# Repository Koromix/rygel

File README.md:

# Projects

As a general rule, applications are licensed under the [GPL 3.0 license](https://www.gnu.org/licenses/gpl-3.0.html), whereas library code is licensed under the [MIT license](https://opensource.org/license/mit).

| Project    | Description                                                                      | Build tool | Quality  | License   |
| ---------- | -------------------------------------------------------------------------------- | ---------- | -------- | --------- |
| *blikk*    | Embeddable beginner-friendly language with static types, fast compilation        | Felix      | **WIP**  | GPL 3     |
| *core*     | Base C++ libraries (such as libcc) and small wrappers (R, rapidjson...)          | Felix      | **Good** | MIT       |
| *cnoke*    | Simple alternative to cmake.js, without any dependency                           | Node.js    | **Good** | MIT       |
| *drd*      | Alternative PMSI MCO classifier, subprojects: libdrd, drdc and drdR              | Felix/R    | **Good** | GPL 3     |
| *felix*    | Small build system made specifically for this repository                         | Felix      | **Good** | GPL 3     |
| *goupile*  | Programmable electronic data capture application                                 | Felix      | **WIP**  | GPL 3     |
| *heimdall* | Interactive timeline visualization UI                                            | Felix/R    | **WIP**  | GPL 3     |
| *hodler*   | Simple markdown-to-HTML website generator (e.g. koromix.dev)                     | Felix      | **Good** | GPL 3     |
| *koffi*    | Fast and simple C FFI (foreign function interface) for Node.js                   | Node.js    | **Good** | MIT       |
| *meestic*  | Control the keyboard lighting on MSI Delta 15 laptops                            | Felix      | **Good** | GPL 3     |
| *napka*    | List and map of mental healthcare resources in France                            | Node.js    | **WIP**  | GPL 3     |
| *redropp*  | File transfer web app with user accounts, SSO and end-to-end encryption          | Felix      | **WIP**  | GPL 3     |
| *rekkord*  | Backup tool with deduplication and asymmetric encryption                         | Felix      | **WIP**  | GPL 3     |
| *thop*     | Web-based institutional PMSI (MCO) reporting tool based on libdrd                | Felix      | **Good** | GPL 3     |
| *tytools*  | Independent tools to manage, flash and communicate with Teensy microcontrollers  | Felix      | **Good** | Unlicense |
| *web*      | Reusable utility functions and HTML/CSS/JS widgets                               | Felix      | **Good** | MIT       |

You can also visit the [attic](src/attic/) for a few more small tools.

# How to build

## C++ projects

Most projects use a dedicated build tool called felix. To get started, you need to build this tool. You can use the bootstrap scripts at the root of the repository to bootstrap it:

* Run `./bootstrap.sh` on Linux and macOS
* Run `bootstrap.bat` on Windows

This will create a felix binary at the root of the source tree. You can then start it to build all projects defined in *FelixBuild.ini*: `felix` on Windows or `./felix` on Linux and macOS.

The following compilers are supported: GCC, Clang and MSVC (on Windows). If you want to build Fast or LTO builds you also need to install Node.js in order to transpile the JS code used in some projects.

Use `./felix --help` for more information.

As of now, R packages cannot be built using this method.

## Node.js projects

Refer to each project (Koffi, etc.) documentation for instructions on how to build these projects.

## R packages

Some packages provide an Rproject file and can be built by R CMD INSTALL. Open the project file (e.g. *src/drd/drdR/drdR.Rproj*) in RStudio and use *Install and restart* in the Build tab.

Provided the needed dependencies are available (including Rtools and Rcpp), it should just work!

# Code style

## Mono repository

I've started using a single repository for all my projects in 2018 because it is easier to manage. There are two killers features for me:

* Cross-project refactoring
* Simplified dependency management

You can find a more detailed rationale here: https://danluu.com/monorepo/

## C++ flavor

Most projects are programmed in C++. I don't use the standard library much (with a few exceptions) and instead rely on my own homegrown cross-platform code, containers and abstractions.

My personal preference goes to a rather C-like C++ style:

- Careful use of templates (mainly for containers)
- Little object-oriented programming, tagged unions and code locality are preferred over inheritance and virtual methods
- Use of defer-like statements for cleanup, or RAII where it feels natural
- No exceptions, errors are logged to stderr (and/or a GUI when one exists) and propagated in the code with a simple return value (bool when possible, a dedicated enum when more information is relevant)
- Memory regions are used when many allocations are needed, when building many strings for example
- Heavy use of array and string views for function arguments
- Avoid dependencies unless a strong argument can be made for one, and vendorize them aggressively (with patches if needed)

I keep watch of all dependencies using GitHub notifications, RSS feeds, mailing lists and visual web page change detection (depending on the project), in order to update them as needed.

> [!NOTE]
> This does not apply to TyTools (and libhs), which are older than the other projects, and were made before I settled on my current programming style.

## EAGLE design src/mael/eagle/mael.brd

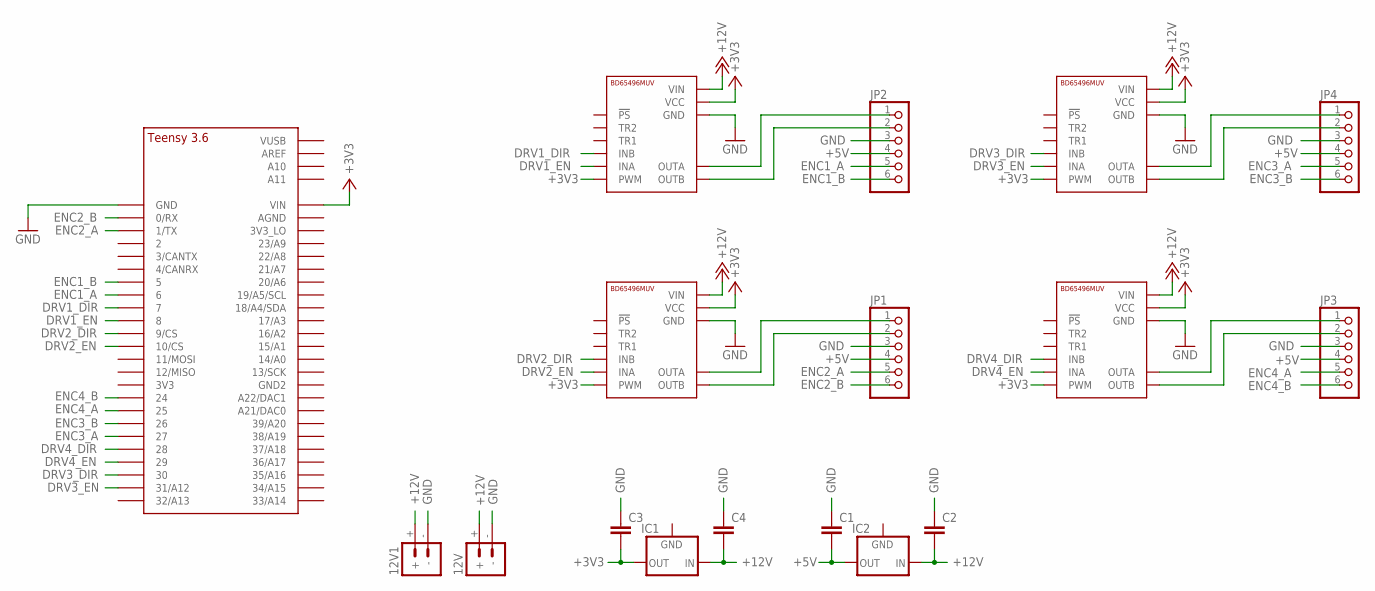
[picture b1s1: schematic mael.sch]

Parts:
12V, 12V1: BATTERY_CONN_DEANS; DEANS
C1, C2, C3, C4: C-EU050-024X044; C050-024X044
IC1, IC2: 78XXL
JP1, JP2, JP3, JP4: PINHD-1X6; 1X06
U$1, U$3, U$4, U$5: BD65496MUV
U$2: TEENSY_3.5/3.6_BASIC

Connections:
+3V3: C3.2, IC1.OUT, U$1.PWM, U$1.VCC, U$2.VIN, U$3.PWM, U$3.VCC, U$4.PWM, U$4.VCC, U$5.PWM, U$5.VCC
+5V: C1.2, IC2.OUT, JP1.4, JP2.4, JP3.4, JP4.4
+12V: 12V.+, 12V1.+, C2.2, C4.2, IC1.IN, IC2.IN, U$1.VIN, U$3.VIN, U$4.VIN, U$5.VIN
DRV1_DIR: U$1.INB, U$2.7
DRV1_EN: U$1.INA, U$2.8
DRV2_DIR: U$2.9/CS, U$3.INB
DRV2_EN: U$2.10/CS, U$3.INA
DRV3_DIR: U$2.30, U$4.INB
DRV3_EN: U$2.31/A12, U$4.INA
DRV4_DIR: U$2.28, U$5.INB
DRV4_EN: U$2.29, U$5.INA
ENC1_A: JP2.5, U$2.6
ENC1_B: JP2.6, U$2.5
ENC2_A: JP1.5, U$2.1/TX
ENC2_B: JP1.6, U$2.0/RX
ENC3_A: JP4.5, U$2.27
ENC3_B: JP4.6, U$2.26
ENC4_A: JP3.5, U$2.25
ENC4_B: JP3.6, U$2.24
GND: 12V.-, 12V1.-, C1.1, C2.1, C3.1, C4.1, JP1.3, JP2.3, JP3.3, JP4.3, U$1.GND1 (GND), U$1.GND2 (GND), U$2.GND, U$3.GND1 (GND), U$3.GND2 (GND), U$4.GND1 (GND), U$4.GND2 (GND), U$5.GND1 (GND), U$5.GND2 (GND)
unnamed: JP4.1, U$4.OUTA
unnamed: JP4.2, U$4.OUTB
unnamed: JP3.2, U$5.OUTB
unnamed: JP3.1, U$5.OUTA
unnamed: JP1.1, U$3.OUTA
unnamed: JP1.2, U$3.OUTB
unnamed: JP2.1, U$1.OUTA
unnamed: JP2.2, U$1.OUTB

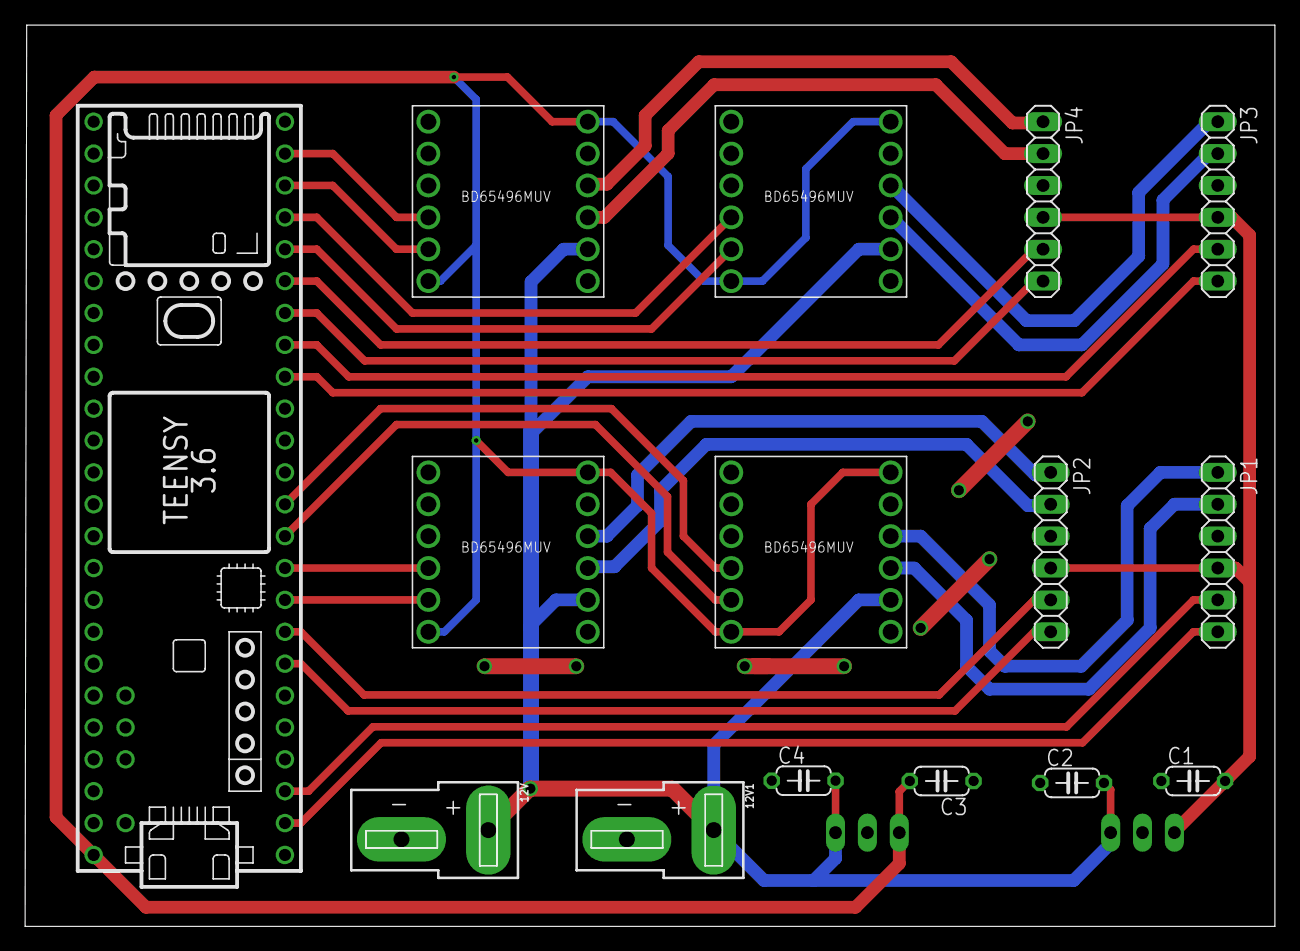
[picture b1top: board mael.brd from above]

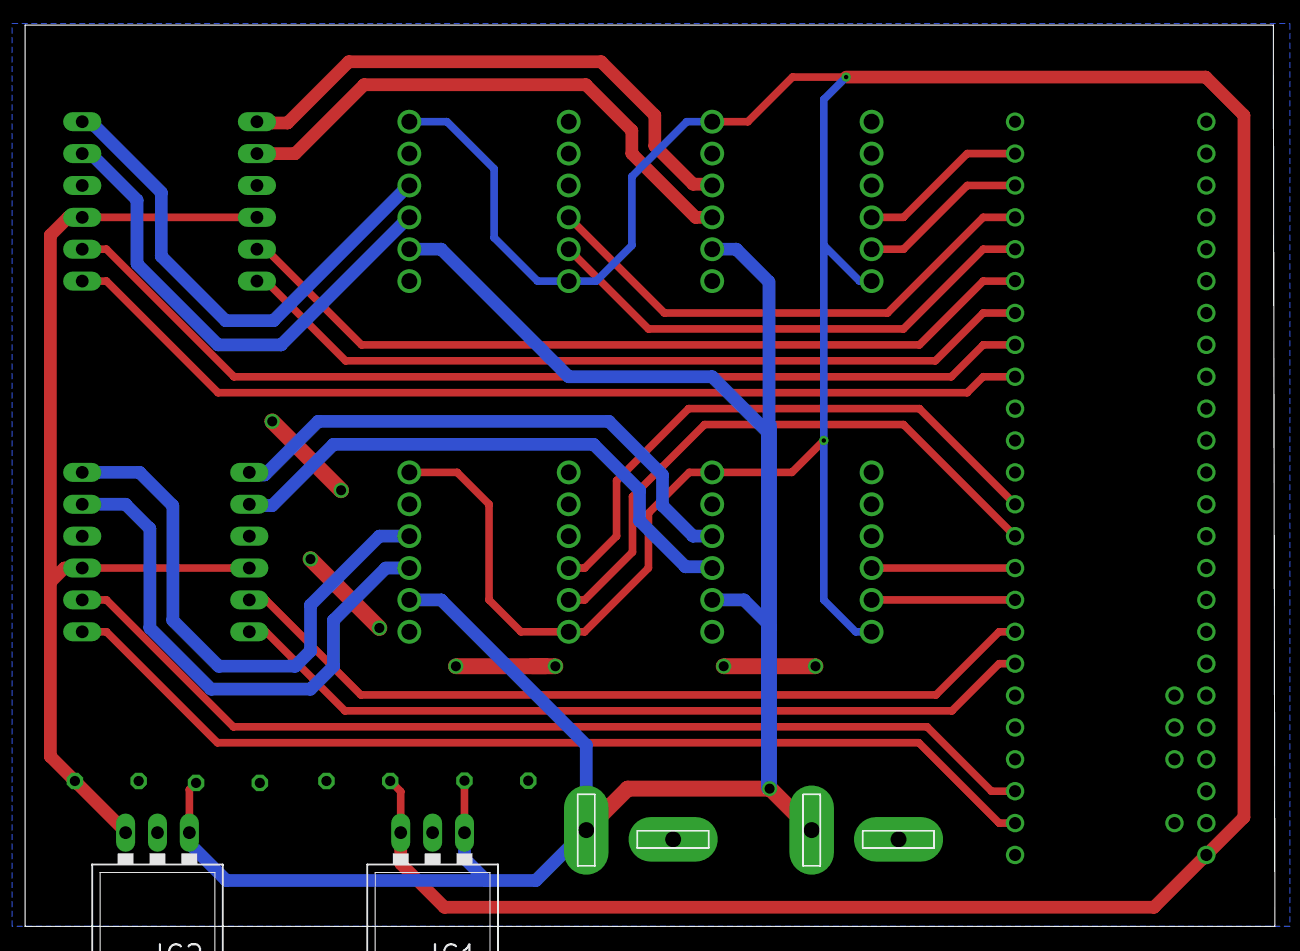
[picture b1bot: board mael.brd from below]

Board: 2 copper layers, 99.6 x 71.8 mm, 17 parts (2 on the bottom side), 28 nets.

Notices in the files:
parts and their libraries:
SparkFun-Connectors: Licensing: Creative Commons ShareAlike 4.0 International - https://creativecommons.org/licenses/by-sa/4.0
